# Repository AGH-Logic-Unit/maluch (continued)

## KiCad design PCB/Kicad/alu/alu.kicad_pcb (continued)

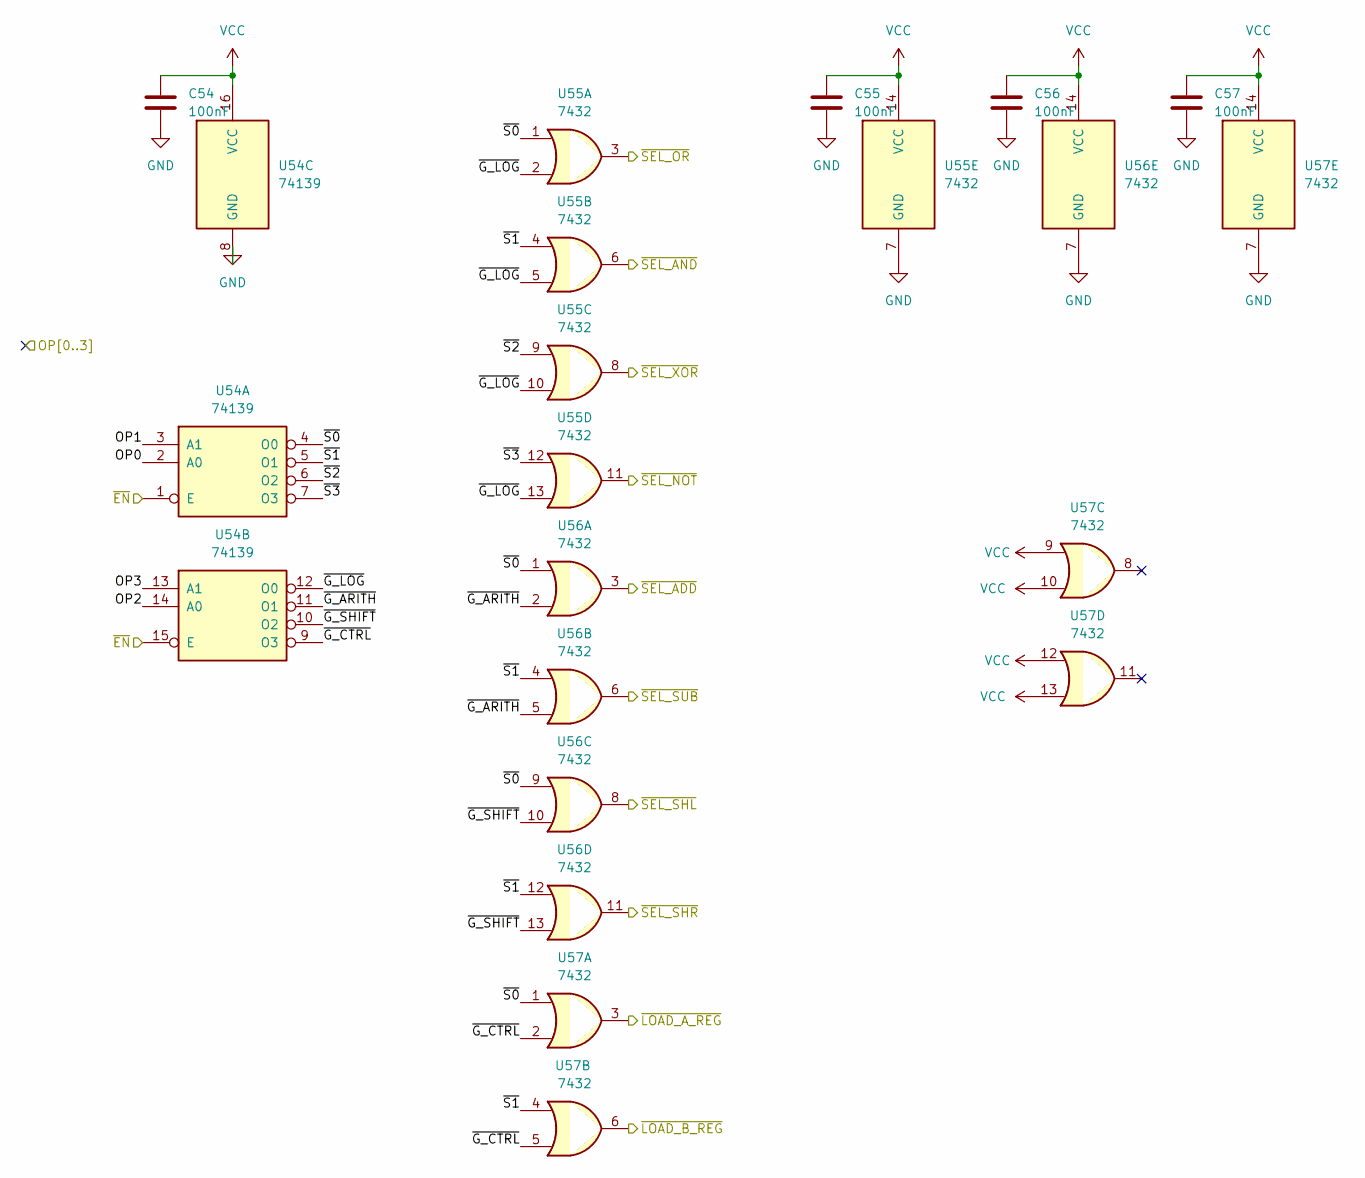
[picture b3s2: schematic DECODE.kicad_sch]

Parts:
C54, C55, C56, C57: 100nF; C_0402_1005Metric
U54: 74139; SOIC-16_3.9x9.9mm_P1.27mm
U55, U56, U57: 7432; SO-14_3.9x8.65mm_P1.27mm

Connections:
/DECODE/~G_ARITH: U54.11 (O1), U56.2, U56.5
/DECODE/~G_CTRL: U54.9 (O3), U57.2, U57.5
/DECODE/~G_LOG: U54.12 (O0), U55.2, U55.5, U55.10, U55.13
/DECODE/~G_SHIFT: U54.10 (O2), U56.10, U56.13
/DECODE/~S0: U54.4 (O0), U55.1, U56.1, U56.9, U57.1
/DECODE/~S1: U54.5 (O1), U55.4, U56.4, U56.12, U57.4
/DECODE/~S2: U54.6 (O2), U55.9
/DECODE/~S3: U54.7 (O3), U55.12
/OP0: U54.2 (A0); also elsewhere on the board
/OP1: U54.3 (A1); also elsewhere on the board
/OP2: U54.14 (A0); also elsewhere on the board
/OP3: U54.13 (A1); also elsewhere on the board
/~LOAD_A_REG: U57.3; also elsewhere on the board
/~LOAD_B_REG: U57.6; also elsewhere on the board
/~SEL_ADD: U56.3; also elsewhere on the board
/~SEL_AND: U55.6; also elsewhere on the board
/~SEL_NOT: U55.11; also elsewhere on the board
/~SEL_OR: U55.3; also elsewhere on the board
/~SEL_SHL: U56.8; also elsewhere on the board
/~SEL_SHR: U56.11; also elsewhere on the board
/~SEL_SUB: U56.6; also elsewhere on the board
/~SEL_XOR: U55.8; also elsewhere on the board
GND: C54.2, C55.2, C56.2, C57.2, U54.1 (E), U54.8 (GND), U54.15 (E), U55.7 (GND), U56.7 (GND), U57.7 (GND); also elsewhere on the board
VCC: C54.1, C55.1, C56.1, C57.1, U54.16 (VCC), U55.14 (VCC), U56.14 (VCC), U57.9, U57.10, U57.12, U57.13, U57.14 (VCC); also elsewhere on the board

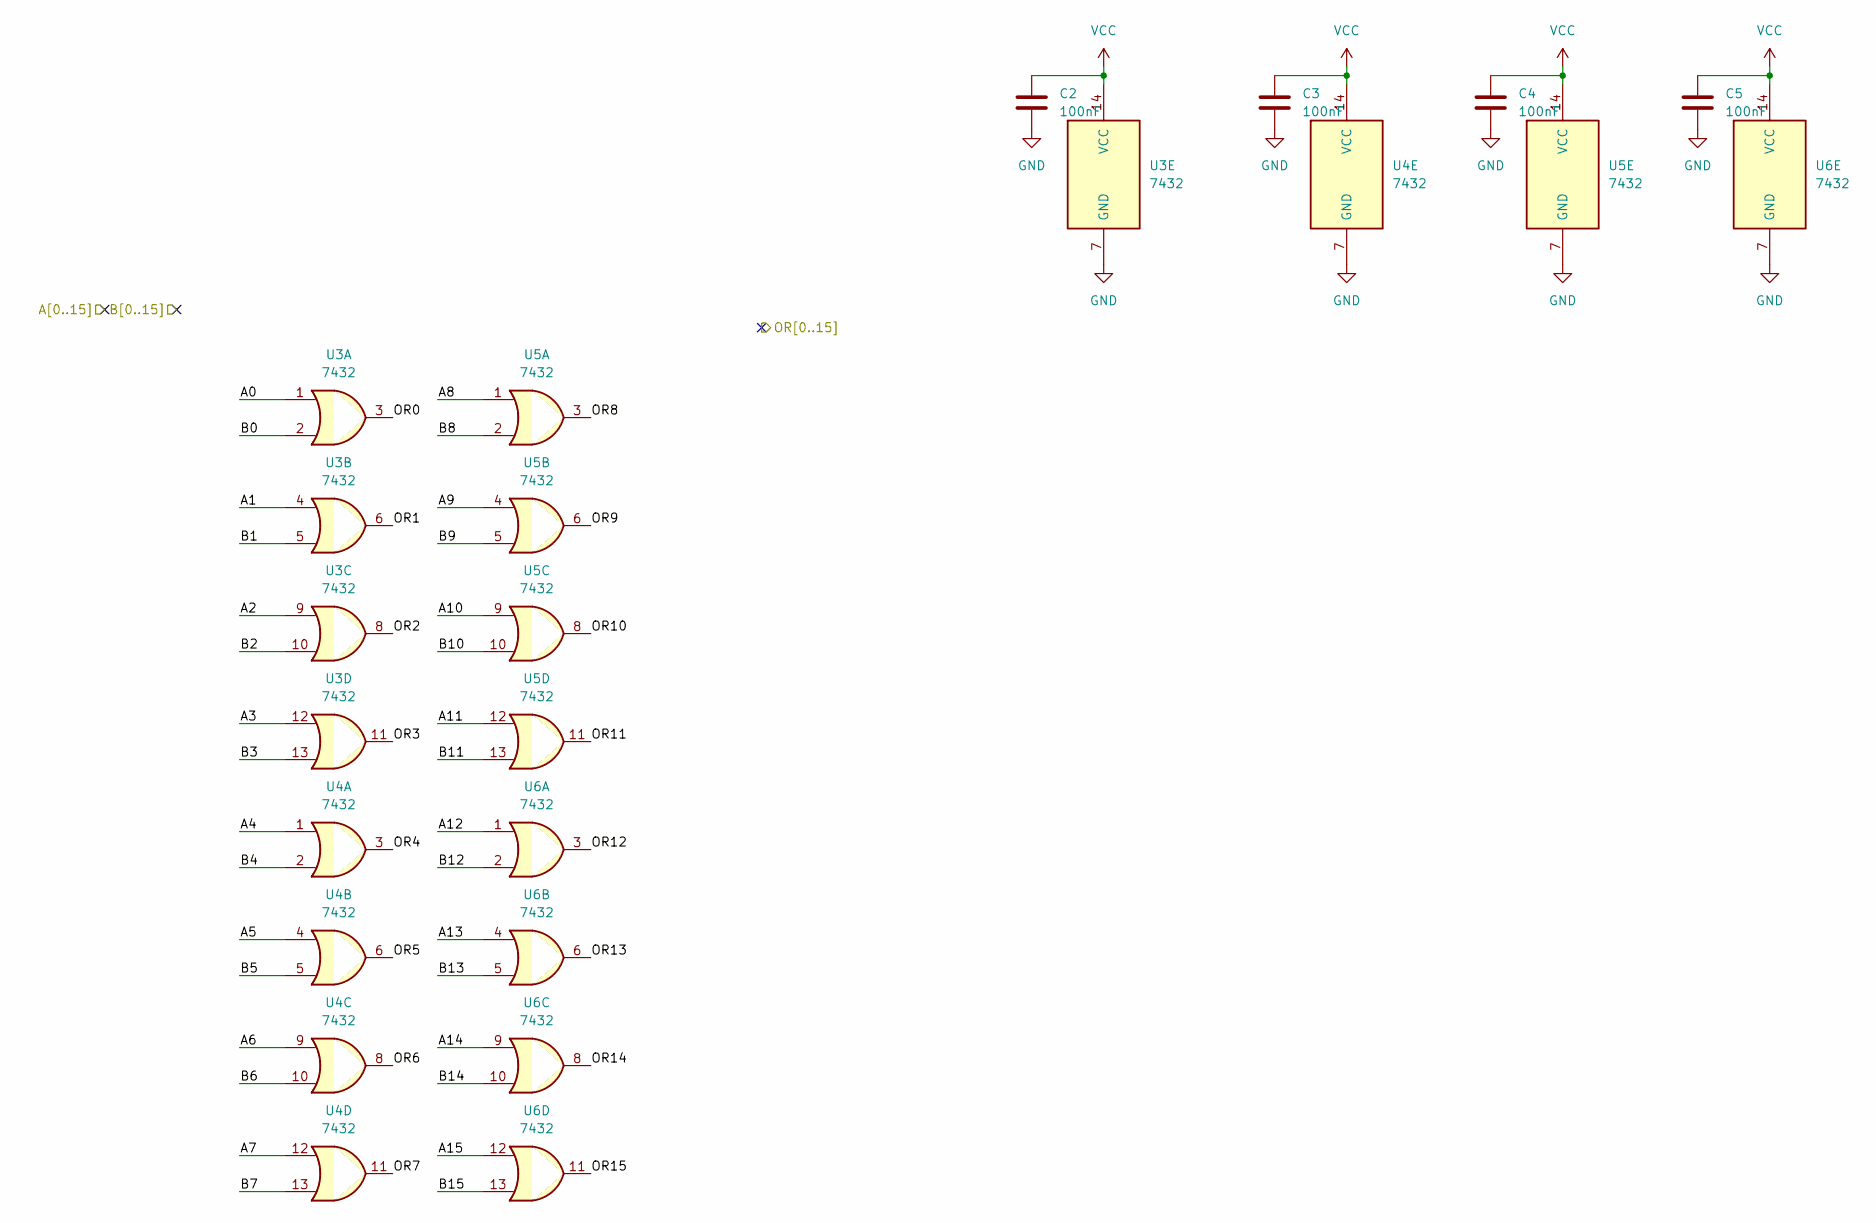
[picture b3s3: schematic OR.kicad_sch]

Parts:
C2, C3, C4, C5: 100nF; C_0402_1005Metric
U3, U4, U5, U6: 7432; SO-14_3.9x8.65mm_P1.27mm

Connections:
/A_BUS0: U3.1; also elsewhere on the board
/A_BUS1: U3.4; also elsewhere on the board
/A_BUS2: U3.9; also elsewhere on the board
/A_BUS3: U3.12; also elsewhere on the board
/A_BUS4: U4.1; also elsewhere on the board
/A_BUS5: U4.4; also elsewhere on the board
/A_BUS6: U4.9; also elsewhere on the board
/A_BUS7: U4.12; also elsewhere on the board
/A_BUS8: U5.1; also elsewhere on the board
/A_BUS9: U5.4; also elsewhere on the board
/A_BUS10: U5.9; also elsewhere on the board
/A_BUS11: U5.12; also elsewhere on the board
/A_BUS12: U6.1; also elsewhere on the board
/A_BUS13: U6.4; also elsewhere on the board
/A_BUS14: U6.9; also elsewhere on the board
/A_BUS15: U6.12; also elsewhere on the board
/B_BUS0: U3.2; also elsewhere on the board
/B_BUS1: U3.5; also elsewhere on the board
/B_BUS2: U3.10; also elsewhere on the board
/B_BUS3: U3.13; also elsewhere on the board
/B_BUS4: U4.2; also elsewhere on the board
/B_BUS5: U4.5; also elsewhere on the board
/B_BUS6: U4.10; also elsewhere on the board
/B_BUS7: U4.13; also elsewhere on the board
/B_BUS8: U5.2; also elsewhere on the board
/B_BUS9: U5.5; also elsewhere on the board
/B_BUS10: U5.10; also elsewhere on the board
/B_BUS11: U5.13; also elsewhere on the board
/B_BUS12: U6.2; also elsewhere on the board
/B_BUS13: U6.5; also elsewhere on the board
/B_BUS14: U6.10; also elsewhere on the board
/B_BUS15: U6.13; also elsewhere on the board
/OR0: U3.3; also elsewhere on the board
/OR1: U3.6; also elsewhere on the board
/OR2: U3.8; also elsewhere on the board
/OR3: U3.11; also elsewhere on the board
/OR4: U4.3; also elsewhere on the board
/OR5: U4.6; also elsewhere on the board
/OR6: U4.8; also elsewhere on the board
/OR7: U4.11; also elsewhere on the board
/OR8: U5.3; also elsewhere on the board
/OR9: U5.6; also elsewhere on the board
/OR10: U5.8; also elsewhere on the board
/OR11: U5.11; also elsewhere on the board
/OR12: U6.3; also elsewhere on the board
/OR13: U6.6; also elsewhere on the board
/OR14: U6.8; also elsewhere on the board
/OR15: U6.11; also elsewhere on the board
GND: C2.2, C3.2, C4.2, C5.2, U3.7 (GND), U4.7 (GND), U5.7 (GND), U6.7 (GND); also elsewhere on the board
VCC: C2.1, C3.1, C4.1, C5.1, U3.14 (VCC), U4.14 (VCC), U5.14 (VCC), U6.14 (VCC); also elsewhere on the board

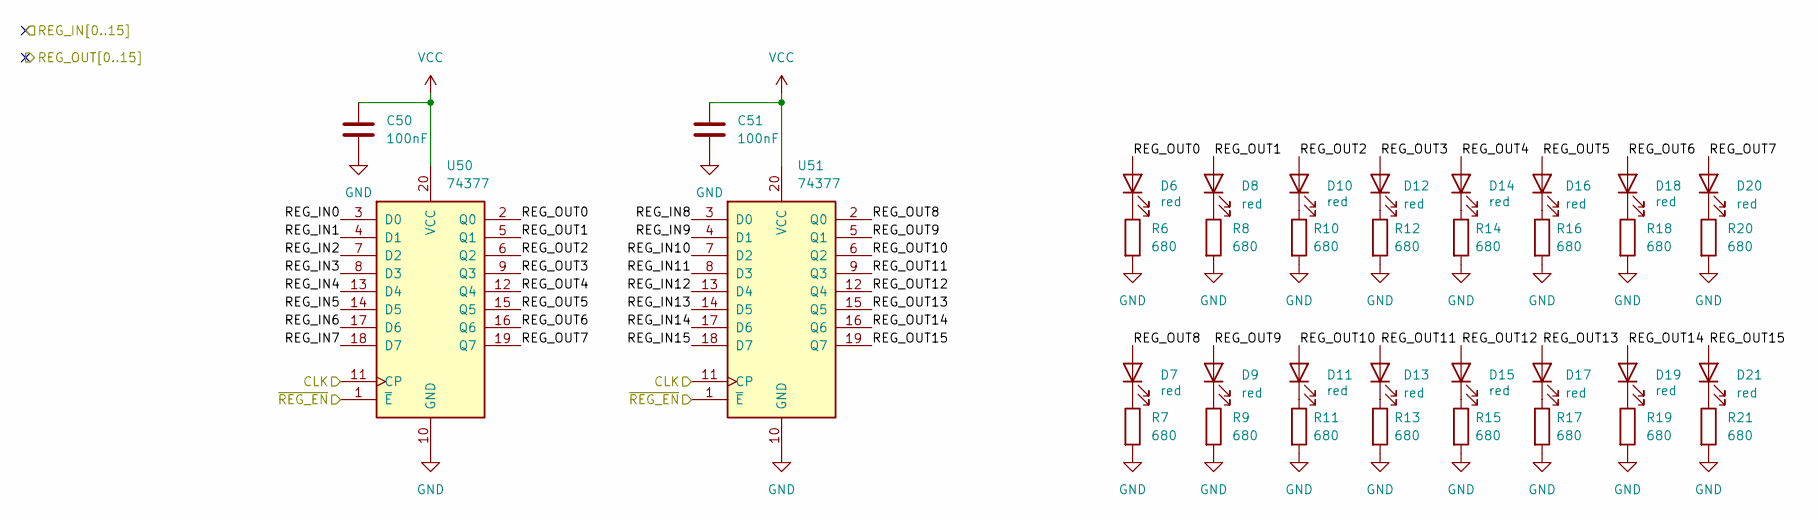
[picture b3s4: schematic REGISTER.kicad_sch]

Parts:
C50, C51: 100nF; C_0402_1005Metric
D6, D7, D8, D9, D10, D11, D12, D13, D14, D15, D16, D17, D18, D19, D20, D21: red; LED_0603_1608Metric
R6, R7, R8, R9, R10, R11, R12, R13, R14, R15, R16, R17, R18, R19, R20, R21: 680; R_0402_1005Metric
U50, U51: 74377; SSOP-20_5.3x7.2mm_P0.65mm

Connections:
/A_BUS0: D6.2 (A), U50.2 (Q0); also elsewhere on the board
/A_BUS1: D8.2 (A), U50.5 (Q1); also elsewhere on the board
/A_BUS2: D10.2 (A), U50.6 (Q2); also elsewhere on the board
/A_BUS3: D12.2 (A), U50.9 (Q3); also elsewhere on the board
/A_BUS4: D14.2 (A), U50.12 (Q4); also elsewhere on the board
/A_BUS5: D16.2 (A), U50.15 (Q5); also elsewhere on the board
/A_BUS6: D18.2 (A), U50.16 (Q6); also elsewhere on the board
/A_BUS7: D20.2 (A), U50.19 (Q7); also elsewhere on the board
/A_BUS8: D7.2 (A), U51.2 (Q0); also elsewhere on the board
/A_BUS9: D9.2 (A), U51.5 (Q1); also elsewhere on the board
/A_BUS10: D11.2 (A), U51.6 (Q2); also elsewhere on the board
/A_BUS11: D13.2 (A), U51.9 (Q3); also elsewhere on the board
/A_BUS12: D15.2 (A), U51.12 (Q4); also elsewhere on the board
/A_BUS13: D17.2 (A), U51.15 (Q5); also elsewhere on the board
/A_BUS14: D19.2 (A), U51.16 (Q6); also elsewhere on the board
/A_BUS15: D21.2 (A), U51.19 (Q7); also elsewhere on the board
/CLK: U50.11 (CP), U51.11 (CP); also elsewhere on the board
/D0: U50.3 (D0); also elsewhere on the board
/D1: U50.4 (D1); also elsewhere on the board
/D2: U50.7 (D2); also elsewhere on the board
/D3: U50.8 (D3); also elsewhere on the board
/D4: U50.13 (D4); also elsewhere on the board
/D5: U50.14 (D5); also elsewhere on the board
/D6: U50.17 (D6); also elsewhere on the board
/D7: U50.18 (D7); also elsewhere on the board
/D8: U51.3 (D0); also elsewhere on the board
/D9: U51.4 (D1); also elsewhere on the board
/D10: U51.7 (D2); also elsewhere on the board
/D11: U51.8 (D3); also elsewhere on the board
/D12: U51.13 (D4); also elsewhere on the board
/D13: U51.14 (D5); also elsewhere on the board
/D14: U51.17 (D6); also elsewhere on the board
/D15: U51.18 (D7); also elsewhere on the board
/~LOAD_A_REG: U50.1 (~E), U51.1 (~E); also elsewhere on the board
GND: C50.2, C51.2, R6.2, R7.2, R8.2, R9.2, R10.2, R11.2, R12.2, R13.2, R14.2, R15.2, R16.2, R17.2, R18.2, R19.2, R20.2, R21.2, U50.10 (GND), U51.10 (GND); also elsewhere on the board
unnamed: D6.1 (K), R6.1
unnamed: D7.1 (K), R7.1
unnamed: D8.1 (K), R8.1
unnamed: D9.1 (K), R9.1
unnamed: D10.1 (K), R10.1
unnamed: D11.1 (K), R11.1
unnamed: D12.1 (K), R12.1
unnamed: D13.1 (K), R13.1
unnamed: D14.1 (K), R14.1
unnamed: D15.1 (K), R15.1
unnamed: D16.1 (K), R16.1
unnamed: D17.1 (K), R17.1
unnamed: D18.1 (K), R18.1
unnamed: D19.1 (K), R19.1
unnamed: D20.1 (K), R20.1
unnamed: D21.1 (K), R21.1
VCC: C50.1, C51.1, U50.20 (VCC), U51.20 (VCC); also elsewhere on the board

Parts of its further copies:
C58, C59: 100nF; C_0402_1005Metric
D22, D23, D24, D25, D26, D27, D28, D29, D30, D31, D32, D33, D34, D35, D36, D37: red; LED_0603_1608Metric
R22, R23, R24, R25, R26, R27, R28, R29, R30, R31, R32, R33, R34, R35, R36, R37: 680; R_0402_1005Metric
U58, U59: 74377; SSOP-20_5.3x7.2mm_P0.65mm

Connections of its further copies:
/B_BUS0: D22.2 (A), U58.2 (Q0); also elsewhere on the board
/B_BUS1: D24.2 (A), U58.5 (Q1); also elsewhere on the board
/B_BUS2: D26.2 (A), U58.6 (Q2); also elsewhere on the board
/B_BUS3: D28.2 (A), U58.9 (Q3); also elsewhere on the board
/B_BUS4: D30.2 (A), U58.12 (Q4); also elsewhere on the board
/B_BUS5: D32.2 (A), U58.15 (Q5); also elsewhere on the board
/B_BUS6: D34.2 (A), U58.16 (Q6); also elsewhere on the board
/B_BUS7: D36.2 (A), U58.19 (Q7); also elsewhere on the board
/B_BUS8: D23.2 (A), U59.2 (Q0); also elsewhere on the board
/B_BUS9: D25.2 (A), U59.5 (Q1); also elsewhere on the board
/B_BUS10: D27.2 (A), U59.6 (Q2); also elsewhere on the board
/B_BUS11: D29.2 (A), U59.9 (Q3); also elsewhere on the board
/B_BUS12: D31.2 (A), U59.12 (Q4); also elsewhere on the board
/B_BUS13: D33.2 (A), U59.15 (Q5); also elsewhere on the board
/B_BUS14: D35.2 (A), U59.16 (Q6); also elsewhere on the board
/B_BUS15: D37.2 (A), U59.19 (Q7); also elsewhere on the board
/CLK: U58.11 (CP), U59.11 (CP); also elsewhere on the board
/D0: U58.3 (D0); also elsewhere on the board
/D1: U58.4 (D1); also elsewhere on the board
/D2: U58.7 (D2); also elsewhere on the board
/D3: U58.8 (D3); also elsewhere on the board
/D4: U58.13 (D4); also elsewhere on the board
/D5: U58.14 (D5); also elsewhere on the board
/D6: U58.17 (D6); also elsewhere on the board
/D7: U58.18 (D7); also elsewhere on the board
/D8: U59.3 (D0); also elsewhere on the board
/D9: U59.4 (D1); also elsewhere on the board
/D10: U59.7 (D2); also elsewhere on the board
/D11: U59.8 (D3); also elsewhere on the board
/D12: U59.13 (D4); also elsewhere on the board
/D13: U59.14 (D5); also elsewhere on the board
/D14: U59.17 (D6); also elsewhere on the board
/D15: U59.18 (D7); also elsewhere on the board
/~LOAD_B_REG: U58.1 (~E), U59.1 (~E); also elsewhere on the board
GND: C58.2, C59.2, R22.2, R23.2, R24.2, R25.2, R26.2, R27.2, R28.2, R29.2, R30.2, R31.2, R32.2, R33.2, R34.2, R35.2, R36.2, R37.2, U58.10 (GND), U59.10 (GND); also elsewhere on the board
unnamed: D22.1 (K), R22.1
unnamed: D23.1 (K), R23.1
unnamed: D24.1 (K), R24.1
unnamed: D25.1 (K), R25.1
unnamed: D26.1 (K), R26.1
unnamed: D27.1 (K), R27.1
unnamed: D28.1 (K), R28.1
unnamed: D29.1 (K), R29.1
unnamed: D30.1 (K), R30.1
unnamed: D31.1 (K), R31.1
unnamed: D32.1 (K), R32.1
unnamed: D33.1 (K), R33.1
unnamed: D34.1 (K), R34.1
unnamed: D35.1 (K), R35.1
unnamed: D36.1 (K), R36.1
unnamed: D37.1 (K), R37.1
VCC: C58.1, C59.1, U58.20 (VCC), U59.20 (VCC); also elsewhere on the board

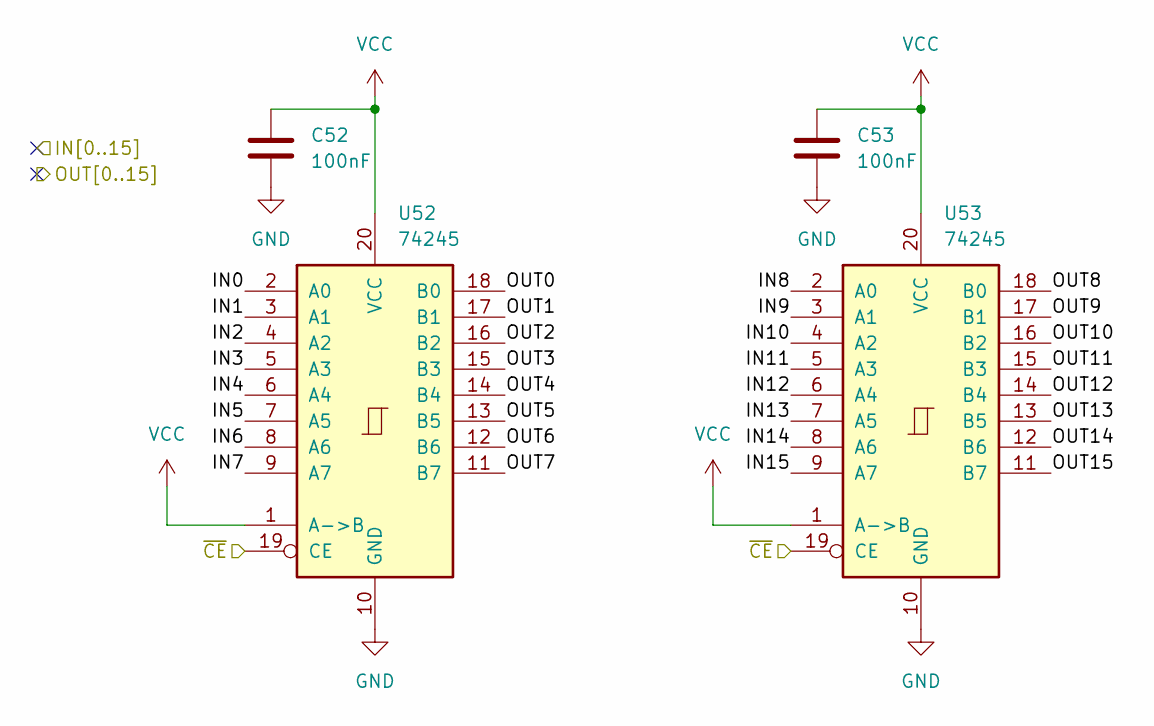
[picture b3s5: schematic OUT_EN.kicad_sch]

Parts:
C52, C53: 100nF; C_0402_1005Metric
U52, U53: 74245; TSSOP-20_4.4x6.5mm_P0.65mm

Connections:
/D0: U52.18 (B0); also elsewhere on the board
/D1: U52.17 (B1); also elsewhere on the board
/D2: U52.16 (B2); also elsewhere on the board
/D3: U52.15 (B3); also elsewhere on the board
/D4: U52.14 (B4); also elsewhere on the board
/D5: U52.13 (B5); also elsewhere on the board
/D6: U52.12 (B6); also elsewhere on the board
/D7: U52.11 (B7); also elsewhere on the board
/D8: U53.18 (B0); also elsewhere on the board
/D9: U53.17 (B1); also elsewhere on the board
/D10: U53.16 (B2); also elsewhere on the board
/D11: U53.15 (B3); also elsewhere on the board
/D12: U53.14 (B4); also elsewhere on the board
/D13: U53.13 (B5); also elsewhere on the board
/D14: U53.12 (B6); also elsewhere on the board
/D15: U53.11 (B7); also elsewhere on the board
/OR0: U52.2 (A0); also elsewhere on the board
/OR1: U52.3 (A1); also elsewhere on the board
/OR2: U52.4 (A2); also elsewhere on the board
/OR3: U52.5 (A3); also elsewhere on the board
/OR4: U52.6 (A4); also elsewhere on the board
/OR5: U52.7 (A5); also elsewhere on the board
/OR6: U52.8 (A6); also elsewhere on the board
/OR7: U52.9 (A7); also elsewhere on the board
/OR8: U53.2 (A0); also elsewhere on the board
/OR9: U53.3 (A1); also elsewhere on the board
/OR10: U53.4 (A2); also elsewhere on the board
/OR11: U53.5 (A3); also elsewhere on the board
/OR12: U53.6 (A4); also elsewhere on the board
/OR13: U53.7 (A5); also elsewhere on the board
/OR14: U53.8 (A6); also elsewhere on the board
/OR15: U53.9 (A7); also elsewhere on the board
/~SEL_OR: U52.19 (CE), U53.19 (CE); also elsewhere on the board
GND: C52.2, C53.2, U52.10 (GND), U53.10 (GND); also elsewhere on the board
VCC: C52.1, C53.1, U52.1 (A->B), U52.20 (VCC), U53.1 (A->B), U53.20 (VCC); also elsewhere on the board

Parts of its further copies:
C60, C61, C62, C63, C64, C65, C66, C67, C68, C69: 100nF; C_0402_1005Metric
U60, U61, U62, U63, U64, U65, U66, U67, U68, U69: 74245; TSSOP-20_4.4x6.5mm_P0.65mm

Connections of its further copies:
/ADD_SUB0: U66.2 (A0); also elsewhere on the board
/ADD_SUB1: U66.3 (A1); also elsewhere on the board
/ADD_SUB2: U66.4 (A2); also elsewhere on the board
/ADD_SUB3: U66.5 (A3); also elsewhere on the board
/ADD_SUB4: U66.6 (A4); also elsewhere on the board
/ADD_SUB5: U66.7 (A5); also elsewhere on the board
/ADD_SUB6: U66.8 (A6); also elsewhere on the board
/ADD_SUB7: U66.9 (A7); also elsewhere on the board
/ADD_SUB8: U67.2 (A0); also elsewhere on the board
/ADD_SUB9: U67.3 (A1); also elsewhere on the board
/ADD_SUB10: U67.4 (A2); also elsewhere on the board
/ADD_SUB11: U67.5 (A3); also elsewhere on the board
/ADD_SUB12: U67.6 (A4); also elsewhere on the board
/ADD_SUB13: U67.7 (A5); also elsewhere on the board
/ADD_SUB14: U67.8 (A6); also elsewhere on the board
/ADD_SUB15: U67.9 (A7); also elsewhere on the board
/AND0: U60.2 (A0); also elsewhere on the board
/AND1: U60.3 (A1); also elsewhere on the board
/AND2: U60.4 (A2); also elsewhere on the board
/AND3: U60.5 (A3); also elsewhere on the board
/AND4: U60.6 (A4); also elsewhere on the board
/AND5: U60.7 (A5); also elsewhere on the board
/AND6: U60.8 (A6); also elsewhere on the board
/AND7: U60.9 (A7); also elsewhere on the board
/AND8: U61.2 (A0); also elsewhere on the board
/AND9: U61.3 (A1); also elsewhere on the board
/AND10: U61.4 (A2); also elsewhere on the board
/AND11: U61.5 (A3); also elsewhere on the board
/AND12: U61.6 (A4); also elsewhere on the board
/AND13: U61.7 (A5); also elsewhere on the board
/AND14: U61.8 (A6); also elsewhere on the board
/AND15: U61.9 (A7); also elsewhere on the board
/D0: U60.18 (B0), U62.18 (B0), U64.18 (B0), U66.18 (B0), U68.18 (B0); also elsewhere on the board
/D1: U60.17 (B1), U62.17 (B1), U64.17 (B1), U66.17 (B1), U68.17 (B1); also elsewhere on the board
/D2: U60.16 (B2), U62.16 (B2), U64.16 (B2), U66.16 (B2), U68.16 (B2); also elsewhere on the board
/D3: U60.15 (B3), U62.15 (B3), U64.15 (B3), U66.15 (B3), U68.15 (B3); also elsewhere on the board
/D4: U60.14 (B4), U62.14 (B4), U64.14 (B4), U66.14 (B4), U68.14 (B4); also elsewhere on the board
/D5: U60.13 (B5), U62.13 (B5), U64.13 (B5), U66.13 (B5), U68.13 (B5); also elsewhere on the board
/D6: U60.12 (B6), U62.12 (B6), U64.12 (B6), U66.12 (B6), U68.12 (B6); also elsewhere on the board
/D7: U60.11 (B7), U62.11 (B7), U64.11 (B7), U66.11 (B7), U68.11 (B7); also elsewhere on the board
/D8: U61.18 (B0), U63.18 (B0), U65.18 (B0), U67.18 (B0), U69.18 (B0); also elsewhere on the board
/D9: U61.17 (B1), U63.17 (B1), U65.17 (B1), U67.17 (B1), U69.17 (B1); also elsewhere on the board
/D10: U61.16 (B2), U63.16 (B2), U65.16 (B2), U67.16 (B2), U69.16 (B2); also elsewhere on the board
/D11: U61.15 (B3), U63.15 (B3), U65.15 (B3), U67.15 (B3), U69.15 (B3); also elsewhere on the board
/D12: U61.14 (B4), U63.14 (B4), U65.14 (B4), U67.14 (B4), U69.14 (B4); also elsewhere on the board
/D13: U61.13 (B5), U63.13 (B5), U65.13 (B5), U67.13 (B5), U69.13 (B5); also elsewhere on the board
/D14: U61.12 (B6), U63.12 (B6), U65.12 (B6), U67.12 (B6), U69.12 (B6); also elsewhere on the board
/D15: U61.11 (B7), U63.11 (B7), U65.11 (B7), U67.11 (B7), U69.11 (B7); also elsewhere on the board
/NOT0: U64.2 (A0); also elsewhere on the board
/NOT1: U64.3 (A1); also elsewhere on the board
/NOT2: U64.4 (A2); also elsewhere on the board
/NOT3: U64.5 (A3); also elsewhere on the board
/NOT4: U64.6 (A4); also elsewhere on the board
/NOT5: U64.7 (A5); also elsewhere on the board
/NOT6: U64.8 (A6); also elsewhere on the board
/NOT7: U64.9 (A7); also elsewhere on the board
/NOT8: U65.2 (A0); also elsewhere on the board
/NOT9: U65.3 (A1); also elsewhere on the board
/NOT10: U65.4 (A2); also elsewhere on the board
/NOT11: U65.5 (A3); also elsewhere on the board
/NOT12: U65.6 (A4); also elsewhere on the board
/NOT13: U65.7 (A5); also elsewhere on the board
/NOT14: U65.8 (A6); also elsewhere on the board
/NOT15: U65.9 (A7); also elsewhere on the board
/SHIFT0: U68.2 (A0); also elsewhere on the board
/SHIFT1: U68.3 (A1); also elsewhere on the board
/SHIFT2: U68.4 (A2); also elsewhere on the board
/SHIFT3: U68.5 (A3); also elsewhere on the board
/SHIFT4: U68.6 (A4); also elsewhere on the board
/SHIFT5: U68.7 (A5); also elsewhere on the board
/SHIFT6: U68.8 (A6); also elsewhere on the board
/SHIFT7: U68.9 (A7); also elsewhere on the board
/SHIFT8: U69.2 (A0); also elsewhere on the board
/SHIFT9: U69.3 (A1); also elsewhere on the board
/SHIFT10: U69.4 (A2); also elsewhere on the board
/SHIFT11: U69.5 (A3); also elsewhere on the board
/SHIFT12: U69.6 (A4); also elsewhere on the board
/SHIFT13: U69.7 (A5); also elsewhere on the board
/SHIFT14: U69.8 (A6); also elsewhere on the board
/SHIFT15: U69.9 (A7); also elsewhere on the board
/XOR0: U62.2 (A0); also elsewhere on the board
/XOR1: U62.3 (A1); also elsewhere on the board
/XOR2: U62.4 (A2); also elsewhere on the board
/XOR3: U62.5 (A3); also elsewhere on the board
/XOR4: U62.6 (A4); also elsewhere on the board
/XOR5: U62.7 (A5); also elsewhere on the board
/XOR6: U62.8 (A6); also elsewhere on the board
/XOR7: U62.9 (A7); also elsewhere on the board
/XOR8: U63.2 (A0); also elsewhere on the board
/XOR9: U63.3 (A1); also elsewhere on the board
/XOR10: U63.4 (A2); also elsewhere on the board
/XOR11: U63.5 (A3); also elsewhere on the board
/XOR12: U63.6 (A4); also elsewhere on the board
/XOR13: U63.7 (A5); also elsewhere on the board
/XOR14: U63.8 (A6); also elsewhere on the board
/XOR15: U63.9 (A7); also elsewhere on the board
/~SEL_ADD_SUB: U66.19 (CE), U67.19 (CE); also elsewhere on the board
/~SEL_AND: U60.19 (CE), U61.19 (CE); also elsewhere on the board
/~SEL_NOT: U64.19 (CE), U65.19 (CE); also elsewhere on the board
/~SEL_SHIFT: U68.19 (CE), U69.19 (CE); also elsewhere on the board
/~SEL_XOR: U62.19 (CE), U63.19 (CE); also elsewhere on the board
GND: C60.2, C61.2, C62.2, C63.2, C64.2, C65.2, C66.2, C67.2, C68.2, C69.2, U60.10 (GND), U61.10 (GND), U62.10 (GND), U63.10 (GND), U64.10 (GND), U65.10 (GND), U66.10 (GND), U67.10 (GND), U68.10 (GND), U69.10 (GND); also elsewhere on the board
VCC: C60.1, C61.1, C62.1, C63.1, C64.1, C65.1, C66.1, C67.1, C68.1, C69.1, U60.1 (A->B), U60.20 (VCC), U61.1 (A->B), U61.20 (VCC), U62.1 (A->B), U62.20 (VCC), U63.1 (A->B), U63.20 (VCC), U64.1 (A->B), U64.20 (VCC), U65.1 (A->B), U65.20 (VCC), U66.1 (A->B), U66.20 (VCC), U67.1 (A->B), U67.20 (VCC), U68.1 (A->B), U68.20 (VCC), U69.1 (A->B), U69.20 (VCC); also elsewhere on the board

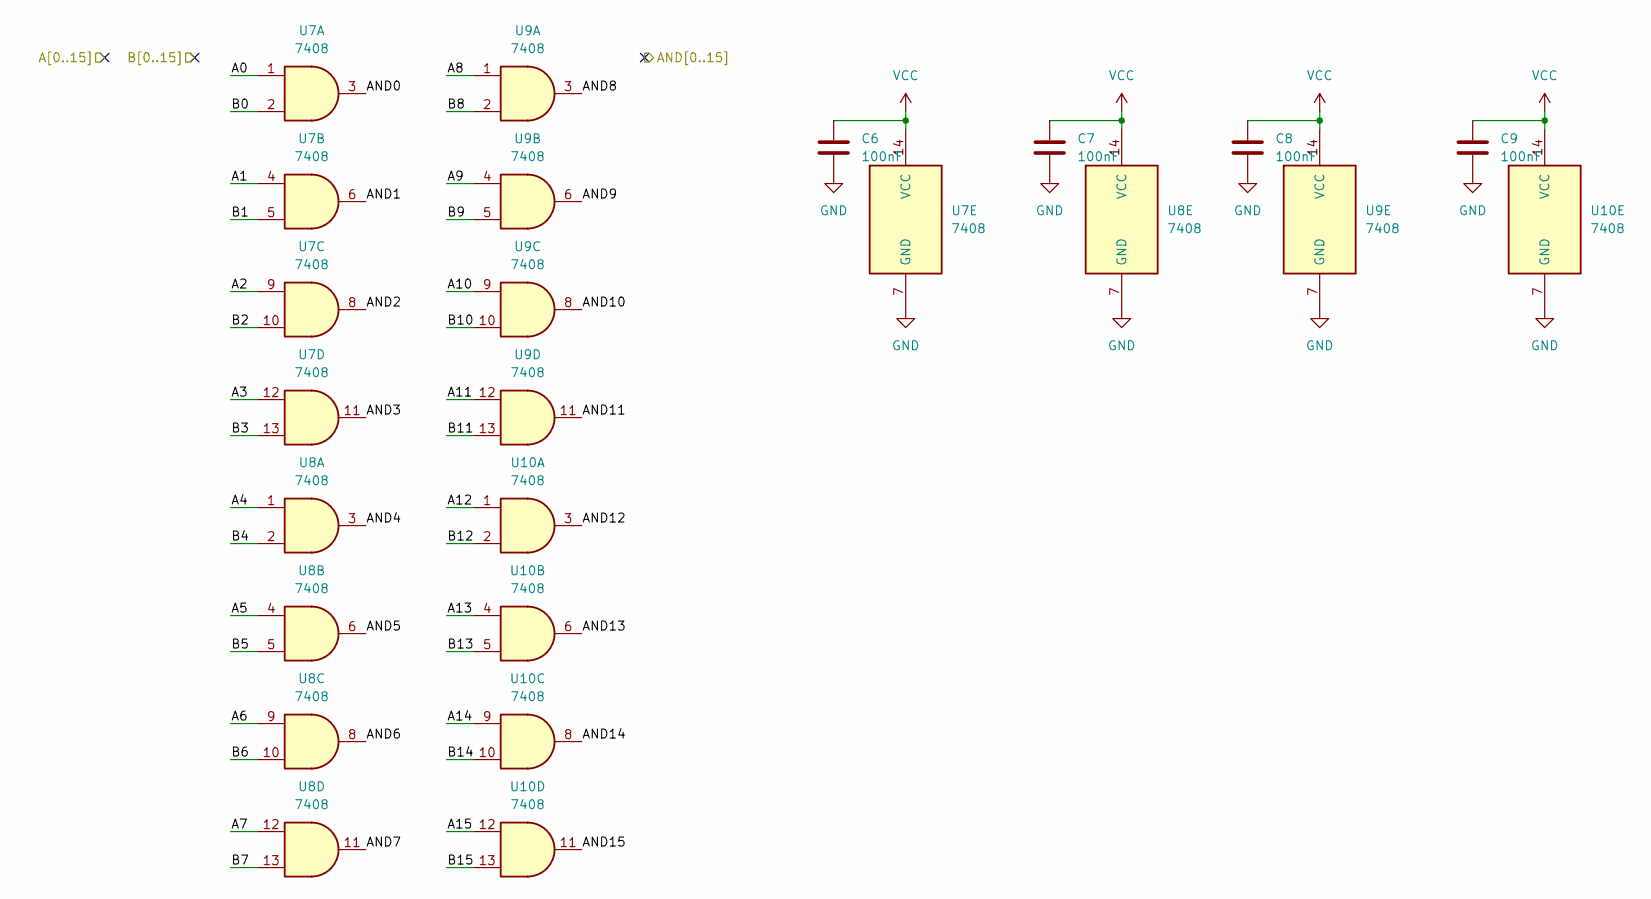
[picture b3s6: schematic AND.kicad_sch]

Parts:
C6, C7, C8, C9: 100nF; C_0402_1005Metric
U7, U8, U9, U10: 7408; SO-14_3.9x8.65mm_P1.27mm

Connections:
/AND0: U7.3; also elsewhere on the board
/AND1: U7.6; also elsewhere on the board
/AND2: U7.8; also elsewhere on the board
/AND3: U7.11; also elsewhere on the board
/AND4: U8.3; also elsewhere on the board
/AND5: U8.6; also elsewhere on the board
/AND6: U8.8; also elsewhere on the board
/AND7: U8.11; also elsewhere on the board
/AND8: U9.3; also elsewhere on the board
/AND9: U9.6; also elsewhere on the board
/AND10: U9.8; also elsewhere on the board
/AND11: U9.11; also elsewhere on the board
/AND12: U10.3; also elsewhere on the board
/AND13: U10.6; also elsewhere on the board
/AND14: U10.8; also elsewhere on the board
/AND15: U10.11; also elsewhere on the board
/A_BUS0: U7.1; also elsewhere on the board
/A_BUS1: U7.4; also elsewhere on the board
/A_BUS2: U7.9; also elsewhere on the board
/A_BUS3: U7.12; also elsewhere on the board
/A_BUS4: U8.1; also elsewhere on the board
/A_BUS5: U8.4; also elsewhere on the board
/A_BUS6: U8.9; also elsewhere on the board
/A_BUS7: U8.12; also elsewhere on the board
/A_BUS8: U9.1; also elsewhere on the board
/A_BUS9: U9.4; also elsewhere on the board
/A_BUS10: U9.9; also elsewhere on the board
/A_BUS11: U9.12; also elsewhere on the board
/A_BUS12: U10.1; also elsewhere on the board
/A_BUS13: U10.4; also elsewhere on the board
/A_BUS14: U10.9; also elsewhere on the board
/A_BUS15: U10.12; also elsewhere on the board
/B_BUS0: U7.2; also elsewhere on the board
/B_BUS1: U7.5; also elsewhere on the board
/B_BUS2: U7.10; also elsewhere on the board
/B_BUS3: U7.13; also elsewhere on the board
/B_BUS4: U8.2; also elsewhere on the board
/B_BUS5: U8.5; also elsewhere on the board
/B_BUS6: U8.10; also elsewhere on the board
/B_BUS7: U8.13; also elsewhere on the board
/B_BUS8: U9.2; also elsewhere on the board
/B_BUS9: U9.5; also elsewhere on the board
/B_BUS10: U9.10; also elsewhere on the board
/B_BUS11: U9.13; also elsewhere on the board
/B_BUS12: U10.2; also elsewhere on the board
/B_BUS13: U10.5; also elsewhere on the board
/B_BUS14: U10.10; also elsewhere on the board
/B_BUS15: U10.13; also elsewhere on the board
GND: C6.2, C7.2, C8.2, C9.2, U7.7 (GND), U8.7 (GND), U9.7 (GND), U10.7 (GND); also elsewhere on the board
VCC: C6.1, C7.1, C8.1, C9.1, U7.14 (VCC), U8.14 (VCC), U9.14 (VCC), U10.14 (VCC); also elsewhere on the board

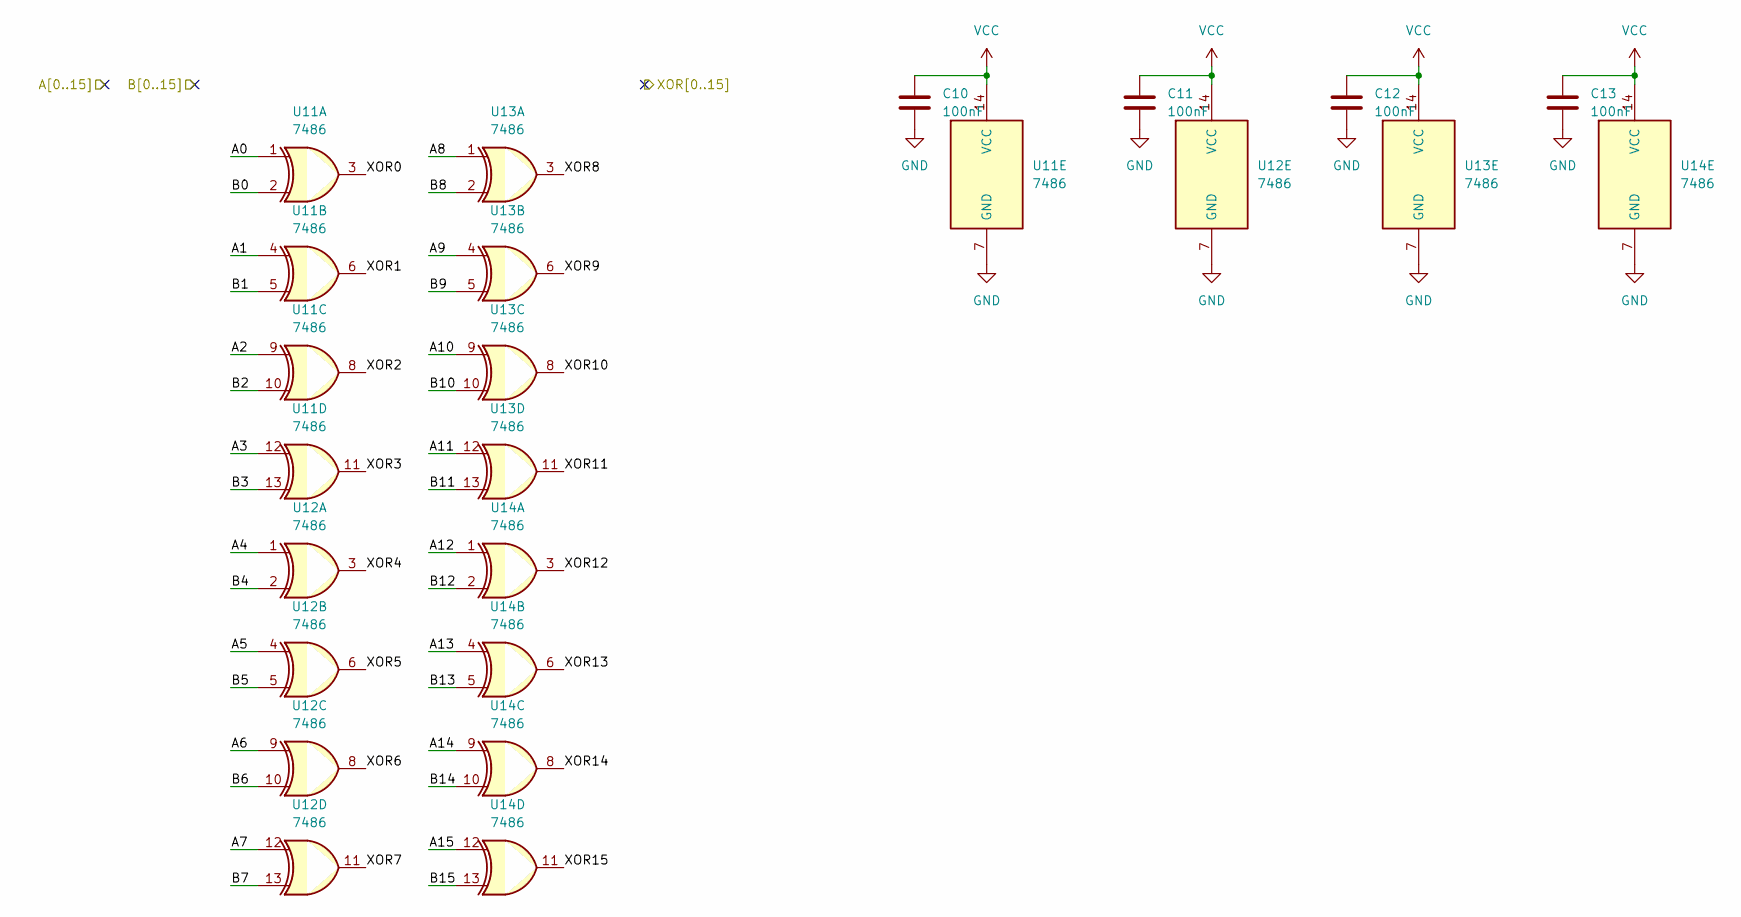
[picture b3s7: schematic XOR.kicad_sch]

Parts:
C10, C11, C12, C13: 100nF; C_0402_1005Metric
U11, U12, U13, U14: 7486; SO-14_3.9x8.65mm_P1.27mm

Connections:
/A_BUS0: U11.1; also elsewhere on the board
/A_BUS1: U11.4; also elsewhere on the board
/A_BUS2: U11.9; also elsewhere on the board
/A_BUS3: U11.12; also elsewhere on the board
/A_BUS4: U12.1; also elsewhere on the board
/A_BUS5: U12.4; also elsewhere on the board
/A_BUS6: U12.9; also elsewhere on the board
/A_BUS7: U12.12; also elsewhere on the board
/A_BUS8: U13.1; also elsewhere on the board
/A_BUS9: U13.4; also elsewhere on the board
/A_BUS10: U13.9; also elsewhere on the board
/A_BUS11: U13.12; also elsewhere on the board
/A_BUS12: U14.1; also elsewhere on the board
/A_BUS13: U14.4; also elsewhere on the board
/A_BUS14: U14.9; also elsewhere on the board
/A_BUS15: U14.12; also elsewhere on the board
/B_BUS0: U11.2; also elsewhere on the board
/B_BUS1: U11.5; also elsewhere on the board
/B_BUS2: U11.10; also elsewhere on the board
/B_BUS3: U11.13; also elsewhere on the board
/B_BUS4: U12.2; also elsewhere on the board
/B_BUS5: U12.5; also elsewhere on the board
/B_BUS6: U12.10; also elsewhere on the board
/B_BUS7: U12.13; also elsewhere on the board
/B_BUS8: U13.2; also elsewhere on the board
/B_BUS9: U13.5; also elsewhere on the board
/B_BUS10: U13.10; also elsewhere on the board
/B_BUS11: U13.13; also elsewhere on the board
/B_BUS12: U14.2; also elsewhere on the board
/B_BUS13: U14.5; also elsewhere on the board
/B_BUS14: U14.10; also elsewhere on the board
/B_BUS15: U14.13; also elsewhere on the board
/XOR0: U11.3; also elsewhere on the board
/XOR1: U11.6; also elsewhere on the board
/XOR2: U11.8; also elsewhere on the board
/XOR3: U11.11; also elsewhere on the board
/XOR4: U12.3; also elsewhere on the board
/XOR5: U12.6; also elsewhere on the board
/XOR6: U12.8; also elsewhere on the board
/XOR7: U12.11; also elsewhere on the board
/XOR8: U13.3; also elsewhere on the board
/XOR9: U13.6; also elsewhere on the board
/XOR10: U13.8; also elsewhere on the board
/XOR11: U13.11; also elsewhere on the board
/XOR12: U14.3; also elsewhere on the board
/XOR13: U14.6; also elsewhere on the board
/XOR14: U14.8; also elsewhere on the board
/XOR15: U14.11; also elsewhere on the board
GND: C10.2, C11.2, C12.2, C13.2, U11.7 (GND), U12.7 (GND), U13.7 (GND), U14.7 (GND); also elsewhere on the board
VCC: C10.1, C11.1, C12.1, C13.1, U11.14 (VCC), U12.14 (VCC), U13.14 (VCC), U14.14 (VCC); also elsewhere on the board
